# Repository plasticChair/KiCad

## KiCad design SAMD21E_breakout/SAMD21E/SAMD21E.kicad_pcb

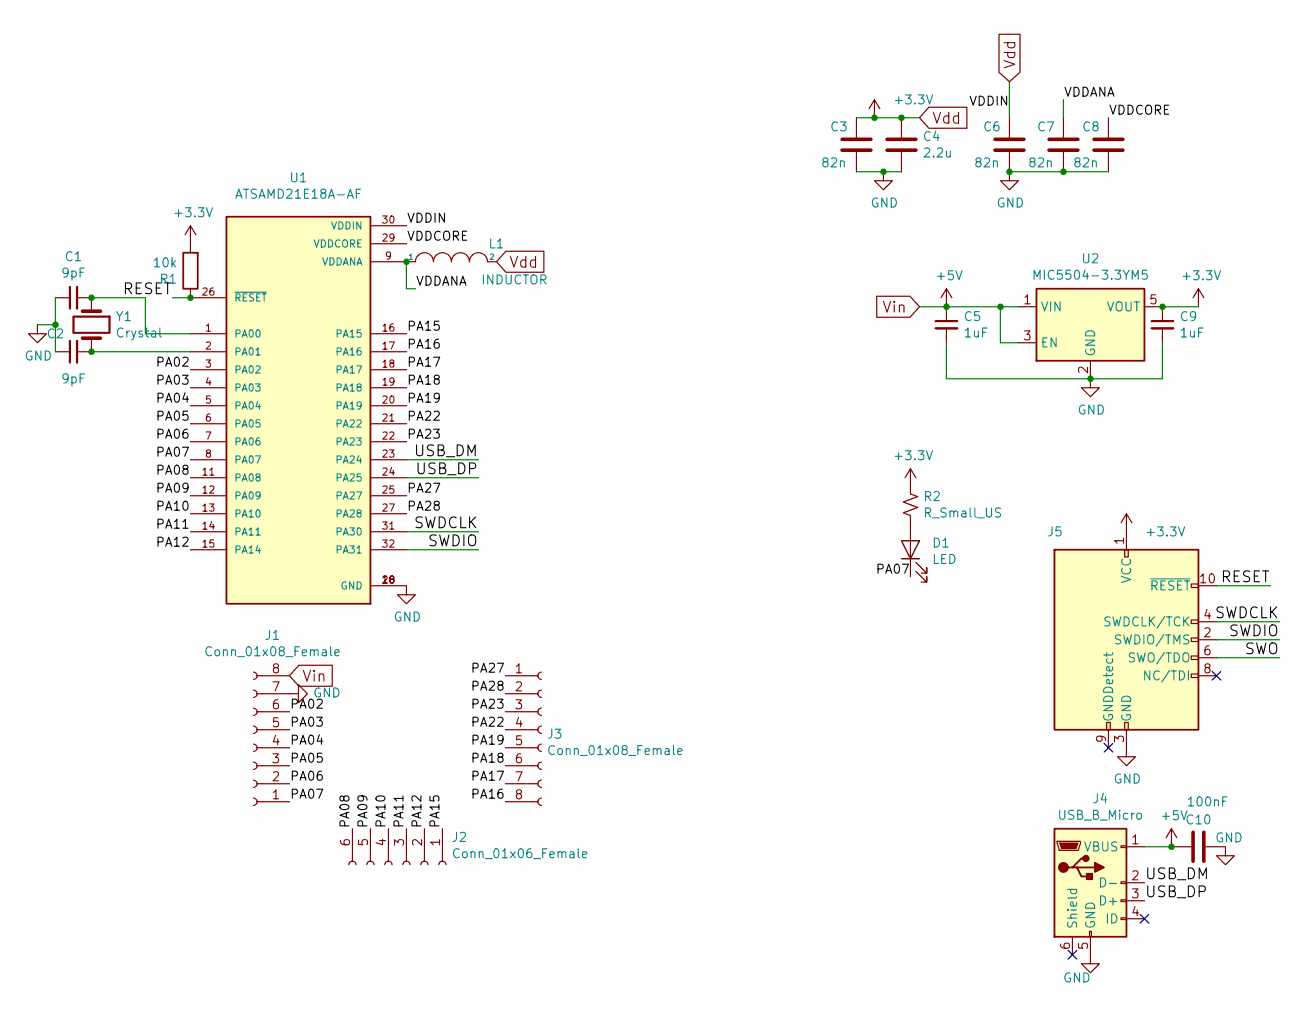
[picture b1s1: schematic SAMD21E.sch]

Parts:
C1, C2: 9pF; C_0603_1608Metric
C3, C6, C7, C8: 82n; C_0805_2012Metric
C4: 2.2u; C_0805_2012Metric
C5, C9: 1uF; C_0603_1608Metric
C10: 100nF; C_0805_2012Metric
D1: LED; LED_0805_2012Metric
J1, J3: Conn_01x08_Female; PinHeader_1x08_P2.54mm_Vertical
J2: Conn_01x06_Female; PinHeader_1x06_P2.54mm_Vertical
J4: USB_B_Micro; USB_Micro-B_Ebay
J5: Conn_ARM_JTAG_SWD_10; PinHeader_2x05_P1.27mm_Vertical_SMD
L1: INDUCTOR; L_0805_2012Metric
R1: 10k; R_0603_1608Metric
R2: R_Small_US; R_0603_1608Metric
U1: ATSAMD21E18A-AF; TQFP32
U2: MIC5504-3.3YM5; SOT-23-5
Y1: Crystal; CM7V-T1A-32.768k-9pF

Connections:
/PA02: J1.6, U1.3 (PA02)
/PA03: J1.5, U1.4 (PA03)
/PA04: J1.4, U1.5 (PA04)
/PA05: J1.3, U1.6 (PA05)
/PA06: J1.2, U1.7 (PA06)
/PA07: D1.1 (K), J1.1, U1.8 (PA07)
/PA08: J2.6, U1.11 (PA08)
/PA09: J2.5, U1.12 (PA09)
/PA10: J2.4, U1.13 (PA10)
/PA11: J2.3, U1.14 (PA11)
/PA12: J2.2, U1.15 (PA14)
/PA15: J2.1, U1.16 (PA15)
/PA16: J3.8, U1.17 (PA16)
/PA17: J3.7, U1.18 (PA17)
/PA18: J3.6, U1.19 (PA18)
/PA19: J3.5, U1.20 (PA19)
/PA22: J3.4, U1.21 (PA22)
/PA23: J3.3, U1.22 (PA23)
/PA27: J3.1, U1.25 (PA27)
/PA28: J3.2, U1.27 (PA28)
/RESET: J5.10 (~RESET~), R1.1, U1.26 (~RESET~)
/SWDCLK: J5.4 (SWDCLK/TCK), U1.31 (PA30)
/SWDIO: J5.2 (SWDIO/TMS), U1.32 (PA31)
/SWO: J5.6 (SWO/TDO)
/USB_DM: J4.2 (D-), U1.23 (PA24)
/USB_DP: J4.3 (D+), U1.24 (PA25)
/VDDANA: C7.1, L1.1, U1.9 (VDDANA)
/VDDCORE: C8.1, U1.29 (VDDCORE)
GND: C1.1, C2.1, C3.2, C4.2, C5.2, C6.2, C7.2, C8.2, C9.2, C10.1, J1.7, J4.5 (GND), J5.3 (GND), J5.5 (GND), U1.10 (GND), U1.28 (GND), U2.2 (GND)
unnamed: C1.2, U1.1 (PA00), Y1.1
unnamed: C2.2, U1.2 (PA01), Y1.2
unnamed: D1.2 (A), R2.2
Vdd: C3.1, C4.1, C6.1, C9.1, J5.1 (VCC), L1.2, R1.2, R2.1, U1.30 (VDDIN), U2.5 (VOUT)
Vin: C5.1, C10.2, J1.8, J4.1 (VBUS), U2.1 (VIN), U2.3 (EN)

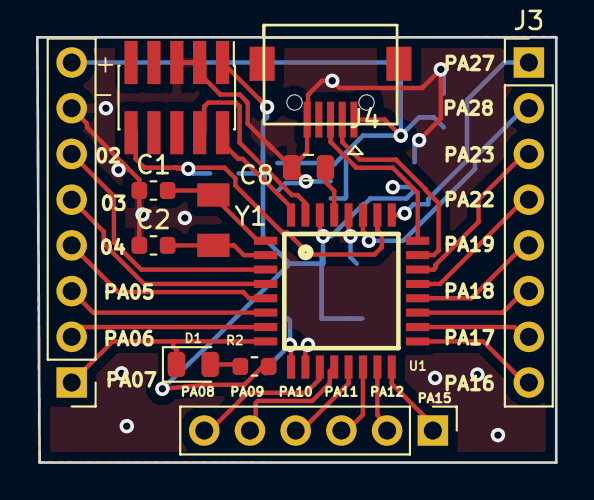
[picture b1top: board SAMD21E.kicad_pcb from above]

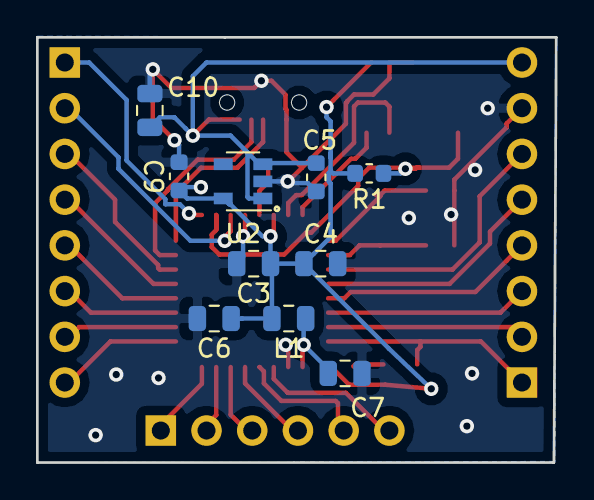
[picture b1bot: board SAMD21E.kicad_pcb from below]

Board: 2 copper layers, 28.8 x 23.6 mm, 22 parts (10 on the bottom side), 33 nets.

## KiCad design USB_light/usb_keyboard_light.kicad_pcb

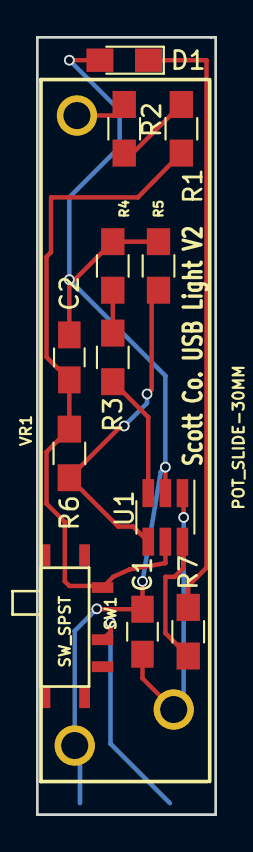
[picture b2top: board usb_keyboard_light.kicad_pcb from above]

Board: 2 copper layers, 9.9 x 43.2 mm, 14 parts (1 on the bottom side), 11 nets.

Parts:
C1, C2: 0.1uF; C_0805_HandSoldering
D1: LED; LED_0805_HandSoldering
J1: Conn_01x02; USBC_breakout
R1, R2, R3, R4, R5, R6, R7: R; R_0805_HandSoldering
SW1: SW_SPST; SWITCH_SPDT_PTH
U1: LTC6992; SOT-23-6_Handsoldering
VR1: POT_SLIDE-30MM; slidingPot

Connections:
GND: C1.1, C2.1, D1.2, J1.2, R4.1, R5.1, U1.2, VR1.TOP
unnamed: C1.2, U1.1, VR1.WIPE
unnamed: D1.1, R7.2
unnamed: J1.1, SW1.2
unnamed: R1.2, R2.1
unnamed: R2.2, VR1.BOTT
unnamed: R3.1, R4.2
unnamed: R3.2, U1.3
unnamed: R5.2, R6.2, U1.4
unnamed: R7.1, U1.6
VDD: C2.2, R1.1, R6.1, SW1.1, U1.5
